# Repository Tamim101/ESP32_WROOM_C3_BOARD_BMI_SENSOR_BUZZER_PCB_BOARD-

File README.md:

3D Board View
<h2>PCB Design Screenshots</h2>

Repository Structure
.
├── ESP32_project.kicad_pro
├── ESP32_project.kicad_sch
├── ESP32_project.kicad_pcb
├── ESP32_project.kicad_prl
├── Libraries/
├── ESP32_project/
├── ESP32_project-backups/
└── images/
    ├── pcb-layout.png
    └── pcb-3d-view.png
Open the Project on Ubuntu
Install KiCad 7 or a compatible newer version.
Clone or download this repository.
Open ESP32_project.kicad_pro in KiCad.
Open the schematic in Schematic Editor or the board in PCB Editor.
Design Validation Before Manufacturing

Before ordering the PCB:

Run Inspect → Electrical Rules Checker (ERC) in Schematic Editor.
Run Inspect → Design Rules Checker (DRC) in PCB Editor.
Fix all errors and confirm there are no unconnected items.
Check connector direction, component orientation, mounting holes, silkscreen, and board outline.
Open KiCad 3D Viewer to inspect component placement.
Generate Gerber and drill files, then inspect them before ordering.
Manufacturing Output

In KiCad PCB Editor:

File → Fabrication Outputs → Gerbers
File → Fabrication Outputs → Drill Files

Upload the Gerber ZIP file to a PCB manufacturer only after completing ERC, DRC, and Gerber inspection.

Initial Hardware Bring-Up

After assembly:

Check for solder bridges, missing parts, and reversed polarity.
Check resistance between power and GND before powering the board.
Use a current-limited bench power supply.
Measure power rails before connecting sensitive modules.
Upload a simple ESP32 test program.
Test the BMI sensor and buzzer separately.
License

No license has been selected yet.# ESP32_WROOM_C3_BOARD_BMI_SENSOR_BUZZER_PCB_BOARD-

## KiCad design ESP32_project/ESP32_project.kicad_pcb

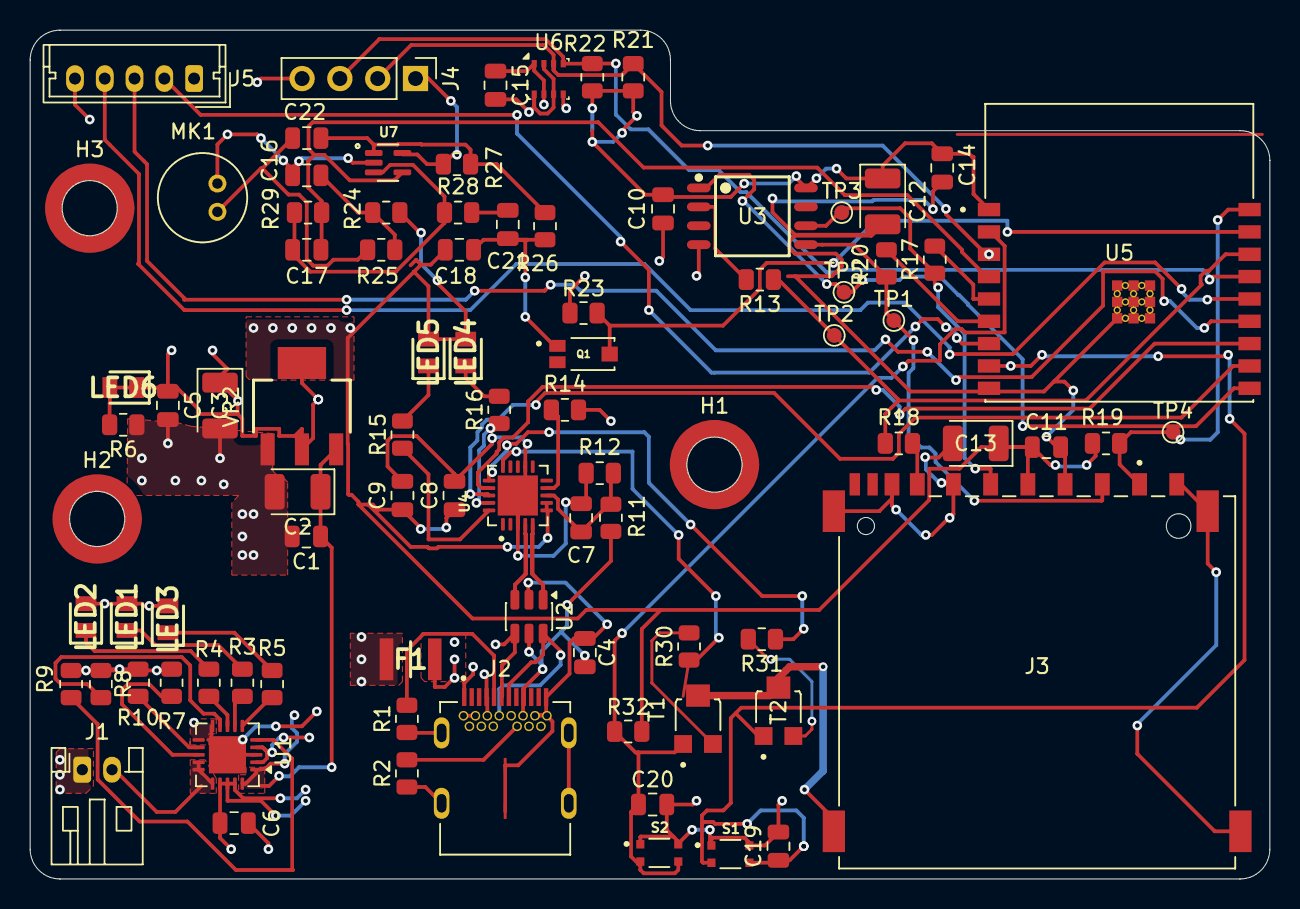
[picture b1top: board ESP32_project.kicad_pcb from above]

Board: 4 copper layers, 83.2 x 57.0 mm, 88 parts (0 on the bottom side), 59 nets.

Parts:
C1, C4, C5, C9, C10, C11, C14, C15, C16, C17, C18, C19: 100nF; C_0805_2012Metric
C2, C3, C12, C13: 10uF; CP_EIA-3528-21_Kemet-B
C6, C7, C20, C21: 1uF; C_0805_2012Metric
C8: 4.7uF; C_0805_2012Metric
C22: 10n; C_0805_2012Metric
F1: 0ZCH0110AF2E; FUSC3226X100N
H1, H2, H3: hole; Mounting_Wuerth_WA-SMSI-M2.5_H1.5mm_9774015151
J1: S2B-PH-K-S(LF)(SN); JST_PH_S2B-PH-K_1x02_P2.00mm_Horizontal
J2: SS-52400-003; BELFUSE_SS-52400-002
J3: GSD090012SEU; AMPHENOL_GSD090012SEU
J4: Conn_01x04_Pin; PinHeader_1x04_P2.54mm_Vertical
J5: Conn_01x05_Pin; Molex_Micro-Latch_53253-0570_1x05_P2.00mm_Vertical
LED1, LED2, LED3, LED4, LED5, LED6: LTST-C170GKT; LEDC2012X120N
MK1: CMC-5042PF-AC; CUI_CMC-5042PF-AC
Q1: TEMT6000X01; TRANS_TEMT6000X01
R1, R2: 5.1K; R_0805_2012Metric
R3, R4, R5, R6, R15, R16: 470; R_0805_2012Metric
R7, R24, R25: 2K; R_0805_2012Metric
R8, R9, R19, R23, R28, R29, R30, R31, R32: 10K; R_0805_2012Metric
R10: 20K; R_0805_2012Metric
R11: 22.1K; R_0805_2012Metric
R12: 47.5K; R_0805_2012Metric
R13, R17, R18, R20: 50; R_0805_2012Metric
R14: 1K; R_0805_2012Metric
R21, R22: 4.7K; R_0805_2012Metric
R26, R27: 1M; R_0805_2012Metric
S1: BOOT; SW_USLPT2819DT2TR
S2: RESET; SW_USLPT2819DT2TR
T1, T2: BC817; TRIM_35WR100KLFTR
TP1: TEST MOSI; TestPoint_Pad_D1.0mm
TP2: TEST MISO; TestPoint_Pad_D1.0mm
TP3: TEST SCLK; TestPoint_Pad_D1.0mm
TP4: TEST CD; TestPoint_Pad_D1.0mm
TP5: TEST CS; TestPoint_Pad_D1.0mm
U1: MCP73871; QFN-20-1EP_4x4mm_P0.5mm_EP2.5x2.5mm
U2: USBLC6-2SC6; SOT-23-6
U3: W25Q32JVSSIQ; SOIC127P790X216-8N
U4: CP2102N-Axx-xQFN20; QFN50P400X400X100-21N
U5: ESP32-C3-WROOM-02-N4; MODULE_ESP32-C3-WROOM-02-H4
U6: BME280; Bosch_LGA-8_2.5x2.5mm_P0.65mm_ClockwisePinNumbering
U7: MAX4466EXK; SOT65P210X110-5N
VR2: LM1117MPX-3.3; VREG_LM1117MPX-3.3

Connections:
+3.3V: C8.1, C9.1, C10.1, C11.1, C12.1, C13.1, C14.1, C15.2, C18.1, J3.4 (VDD1), J4.1, J5.1, LED4.2, LED5.2, R14.1, R19.2, R21.1, R22.1, R23.1, R24.2, R27.2, R32.2, U3.8 (VCC), U4.6 (VDD), U4.7 (VREGIN), U5.1 (3V3), U6.2 (CSB), U6.6 (VDDIO), U6.8 (VDD), U7.5 (VCC)
+3V3: C3.1, C5.1, LED6.1, VR2.2 (VOUT_2), VR2.4 (VOUT_4)
+5V: C1.1, C2.1, U1.1 (OUT), U1.20 (OUT), VR2.3 (VIN)
/+5V_USB: C6.1, F1.2, LED1.2, LED2.2, LED3.2, U1.2 (VPCC), U1.4 (PROG2), U1.17 (CE), U1.18 (IN), U1.19 (IN)
/CHARGED: R4.1, U1.8 (STAT1/~LBO)
/CHARGING: R5.1, U1.6 (~PG)
/CHARGING_POWER_GOOD: R3.1, U1.7 (STAT2)
/USB_DN: J2.A7 (DN1), J2.B7 (DN2), U2.6 (I/O1)
/USB_DP: J2.A6 (DP1), J2.B6 (DP2), U2.4 (I/O2)
/VBAT: J1.2, U1.14 (V_{BAT}), U1.15 (V_{BAT}), U1.16 (V_{BAT_SENSE})
/VBUS: C4.1, F1.1, J2.A4 (VBUSA1), J2.A9 (VBUSA2), J2.B4 (VBUSB1), J2.B9 (VBUSB2), R11.1, U2.5 (VBUS)
/esp32 c3 0.2/BOOT: C19.1, S1.3, S1.4, T2.1, U5.8 (IO9)
/esp32 c3 0.2/CS: TP5.1, U3.1 (~CS), U5.10 (IO10)
/esp32 c3 0.2/CS_SD: J3.1 (CD/DAT3), R19.1, TP4.1, U5.18 (IO0)
/esp32 c3 0.2/DTR: R30.1, U4.15 (~CTS)
/esp32 c3 0.2/EN: C20.1, R32.1, S2.3, S2.4, T1.1, U5.2 (EN)
/esp32 c3 0.2/GPIO8: J5.2, U5.7 (IO8)
/esp32 c3 0.2/GPIO18: J5.3, U5.13 (IO18)
/esp32 c3 0.2/GPIO19: J5.4, U5.14 (IO19)
/esp32 c3 0.2/MIC_OUT: C17.2, R29.2, U5.4 (IO5), U7.4 (OUT)
/esp32 c3 0.2/MISO_DO: R13.1, R18.2, TP2.1, U5.16 (IO2)
/esp32 c3 0.2/MOSI_DI: J3.2 (CMD), R20.2, TP1.1, U3.5 (DI(IO0))
/esp32 c3 0.2/PHOTO_C: Q1.3, R23.2, U5.17 (IO1)
/esp32 c3 0.2/RTS: R31.1, U4.16 (~RTS)
/esp32 c3 0.2/RX_TX: U4.17 (RXD), U5.12 (TXD)
/esp32 c3 0.2/SCL: J4.3, R22.2, U5.15 (IO3), U6.4 (SCK)
/esp32 c3 0.2/SCLK: J3.5 (CLK), R17.1, TP3.1, U3.6 (CLK)
/esp32 c3 0.2/SDA: J4.2, R21.2, U5.3 (IO4), U6.3 (SDI)
/esp32 c3 0.2/TX_RX: U4.18 (TXD), U5.11 (RXD)
/esp32 c3 0.2/USB_D+: U2.3 (I/O2), U4.4 (D+)
/esp32 c3 0.2/USB_D-: U2.1 (I/O1), U4.5 (D-)
GND: C1.2, C2.2, C3.2, C4.2, C5.2, C6.2, C7.2, C8.2, C9.2, C10.2, C11.2, C12.2, C13.2, C14.2, C15.1, C16.1, C18.2, C19.2, C20.2, C21.1, J1.1, J2.A1 (GNDA1), J2.A12 (GNDA2), J2.B1 (GNDB1), J2.B12 (GNDB2), J2.G1 (GND/SHIELD), J2.G2 (GND/SHIELD), J2.G3 (GND/SHIELD), J2.G4 (GND/SHIELD), J2.S1 (GND/SHIELD), J2.S2 (GND/SHIELD), J2.S3 (GND/SHIELD), J2.S4 (GND/SHIELD), J3.3 (VSS1), J3.6 (VSS2), J3.8 (DAT1), J3.9 (DAT2), J3.G1 (SHIELD_GND), J3.G2 (SHIELD_GND), J3.G3 (SHIELD_GND), J3.G4 (SHIELD_GND), J4.4, J5.5, MK1.GND, Q1.1, R1.1, R2.1, R6.1, R7.1, R8.2, R9.2, R10.1, R12.2, R26.1, S1.1, S1.2, S2.1, S2.2, T1.2, T2.2, U1.3 (SEL), U1.10 (V_{SS}), U1.11 (V_{SS}), U1.21 (V_{SS}), U2.2 (GND), U3.4 (GND), U4.3 (GND), U4.12 (GND), U4.21 (GND), U5.9 (GND), U5.19 (GND), U5.20 (GND), U5.21 (GND), U5.22 (GND), U5.23 (GND), U5.24 (GND), U5.25 (GND), U5.26 (GND), U5.27 (GND), U5.28 (GND), U5.29 (GND), U5.30 (GND), U5.31 (GND), U5.32 (GND), U5.33 (GND), U5.34 (GND), U5.35 (GND), U5.36 (GND), U5.37 (GND), U5.38 (GND), U5.39 (GND), U6.1 (GND), U6.5 (SDO), U6.7 (GND), U7.2 (GND), VR2.1 (GND)
unnamed: C16.2, R24.1, R25.2
unnamed: C21.2, R28.1
unnamed: C22.2, MK1.OUT, R25.1
unnamed: J2.A5 (CC1), R1.2
unnamed: J2.B5 (CC2), R2.2
unnamed: J3.7 (DAT0), R18.1
unnamed: LED1.1, R3.2
unnamed: LED2.1, R4.2
unnamed: LED3.1, R5.2
unnamed: LED4.1, R16.2
unnamed: LED5.1, R15.2
unnamed: LED6.2, R6.2
unnamed: R30.2, T1.3
unnamed: R31.2, T2.3
unnamed: R7.2, U1.13 (PROG1)
unnamed: R10.2, U1.12 (PROG3)
unnamed: R9.1, U1.5 (THERM)
unnamed: R8.1, U1.9 (~TE)
unnamed: R13.2, U3.2 (DO(IO1))
unnamed: C7.1, R11.2, R12.1, U4.8 (VBUS)
unnamed: R14.2, U4.9 (~RST)
unnamed: R16.1, U4.19 (~RXT/GPIO.3)
unnamed: R15.1, U4.20 (~TXT/GPIO.2)
unnamed: R17.2, U5.5 (IO6)
unnamed: R20.1, U5.6 (IO7)
unnamed: C22.1, R26.2, R27.1, U7.1 (IN+)
unnamed: C17.1, R28.2, R29.1, U7.3 (IN-)

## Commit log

2026-06-24 update pcb
2026-06-24 update pcb Image
2026-06-24 Enhance README with PCB design and usage instructions
    Added detailed PCB design information, repository structure, and manufacturing instructions.
